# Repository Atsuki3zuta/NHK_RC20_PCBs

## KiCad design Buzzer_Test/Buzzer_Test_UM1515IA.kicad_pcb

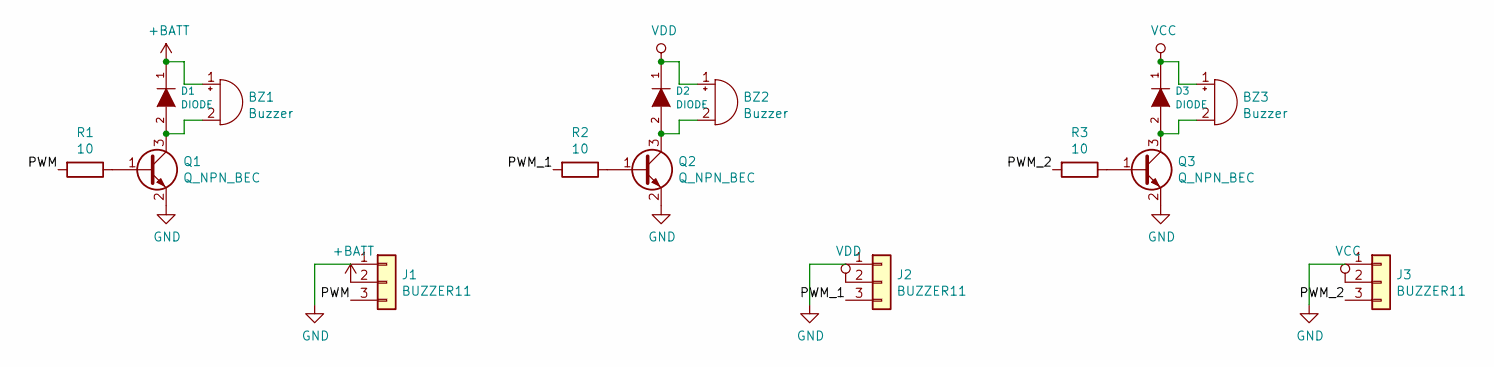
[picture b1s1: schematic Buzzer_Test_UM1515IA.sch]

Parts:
BZ1: Buzzer; UM1515IA
BZ2: Buzzer; UGCT7525AN4
BZ3: Buzzer; PKLCS1212E4001
D1, D2, D3: DIODE; D_SOD-123
J1, J2, J3: BUZZER11; PinHeader_1x03_P2.54mm_Vertical
Q1, Q2, Q3: Q_NPN_BEC; SOT-23W
R1, R2, R3: 10; R_0603_1608Metric

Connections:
+BATT: BZ1.1 (-), D1.1 (K), J1.2
/PWM: J1.3, R1.2
/PWM_1: J2.3, R2.2
/PWM_2: J3.3, R3.2
GND: J1.1, J2.1, J3.1, Q1.2 (E), Q2.2 (E), Q3.2 (E)
unnamed: BZ1.2 (+), D1.2 (A), Q1.3 (C)
unnamed: BZ2.2 (+), D2.2 (A), Q2.3 (C)
unnamed: BZ3.2 (+), D3.2 (A), Q3.3 (C)
unnamed: Q1.1 (B), R1.1
unnamed: Q2.1 (B), R2.1
unnamed: Q3.1 (B), R3.1
VCC: BZ3.1 (-), D3.1 (K), J3.2
VDD: BZ2.1 (-), D2.1 (K), J2.2

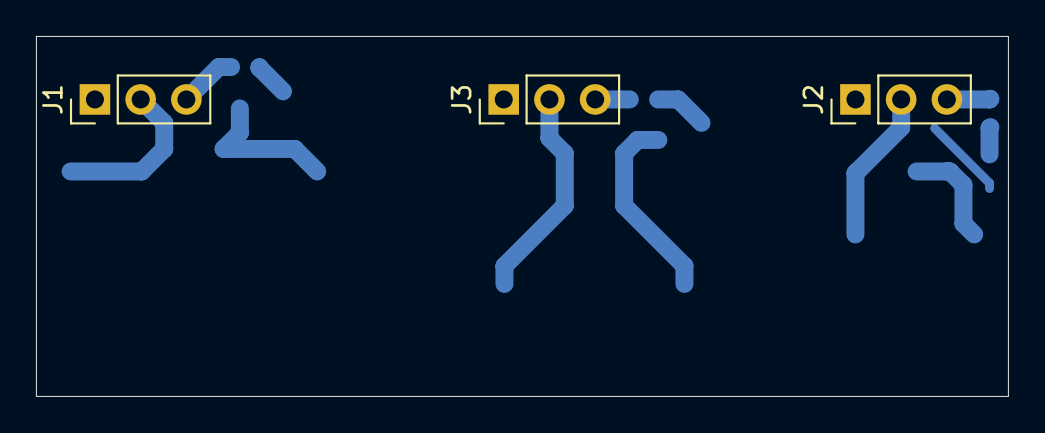
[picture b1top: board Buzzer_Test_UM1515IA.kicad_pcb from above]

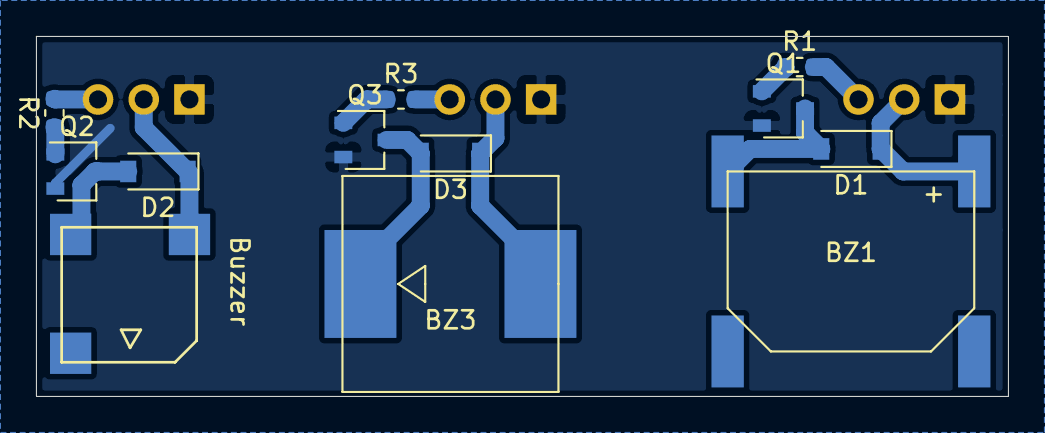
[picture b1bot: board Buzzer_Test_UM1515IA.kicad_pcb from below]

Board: 2 copper layers, 54.0 x 20.0 mm, 15 parts (12 on the bottom side), 13 nets.

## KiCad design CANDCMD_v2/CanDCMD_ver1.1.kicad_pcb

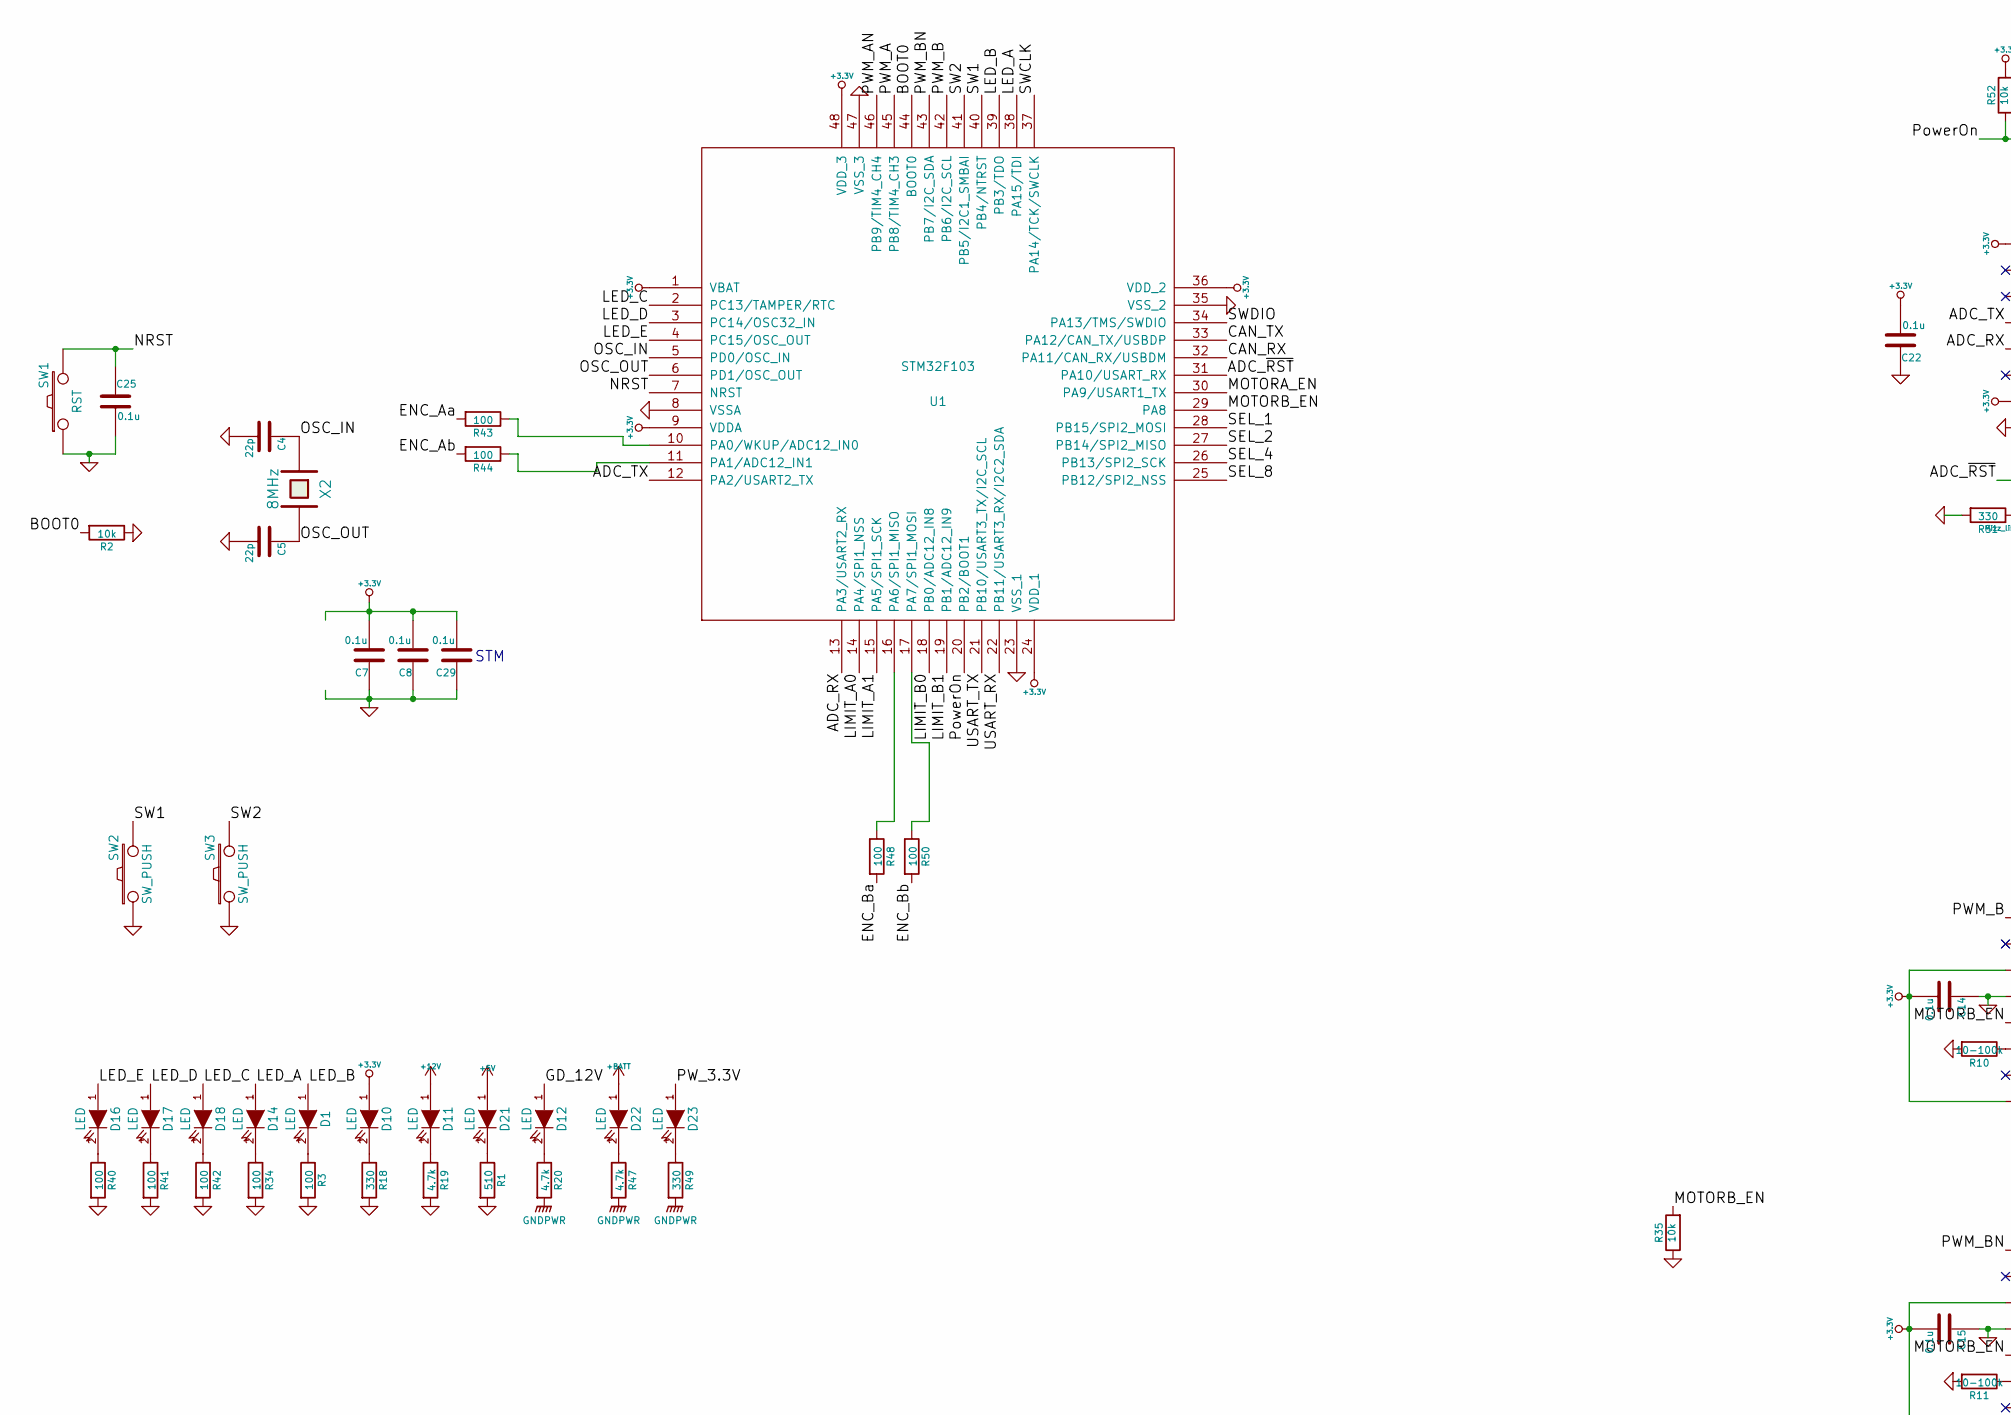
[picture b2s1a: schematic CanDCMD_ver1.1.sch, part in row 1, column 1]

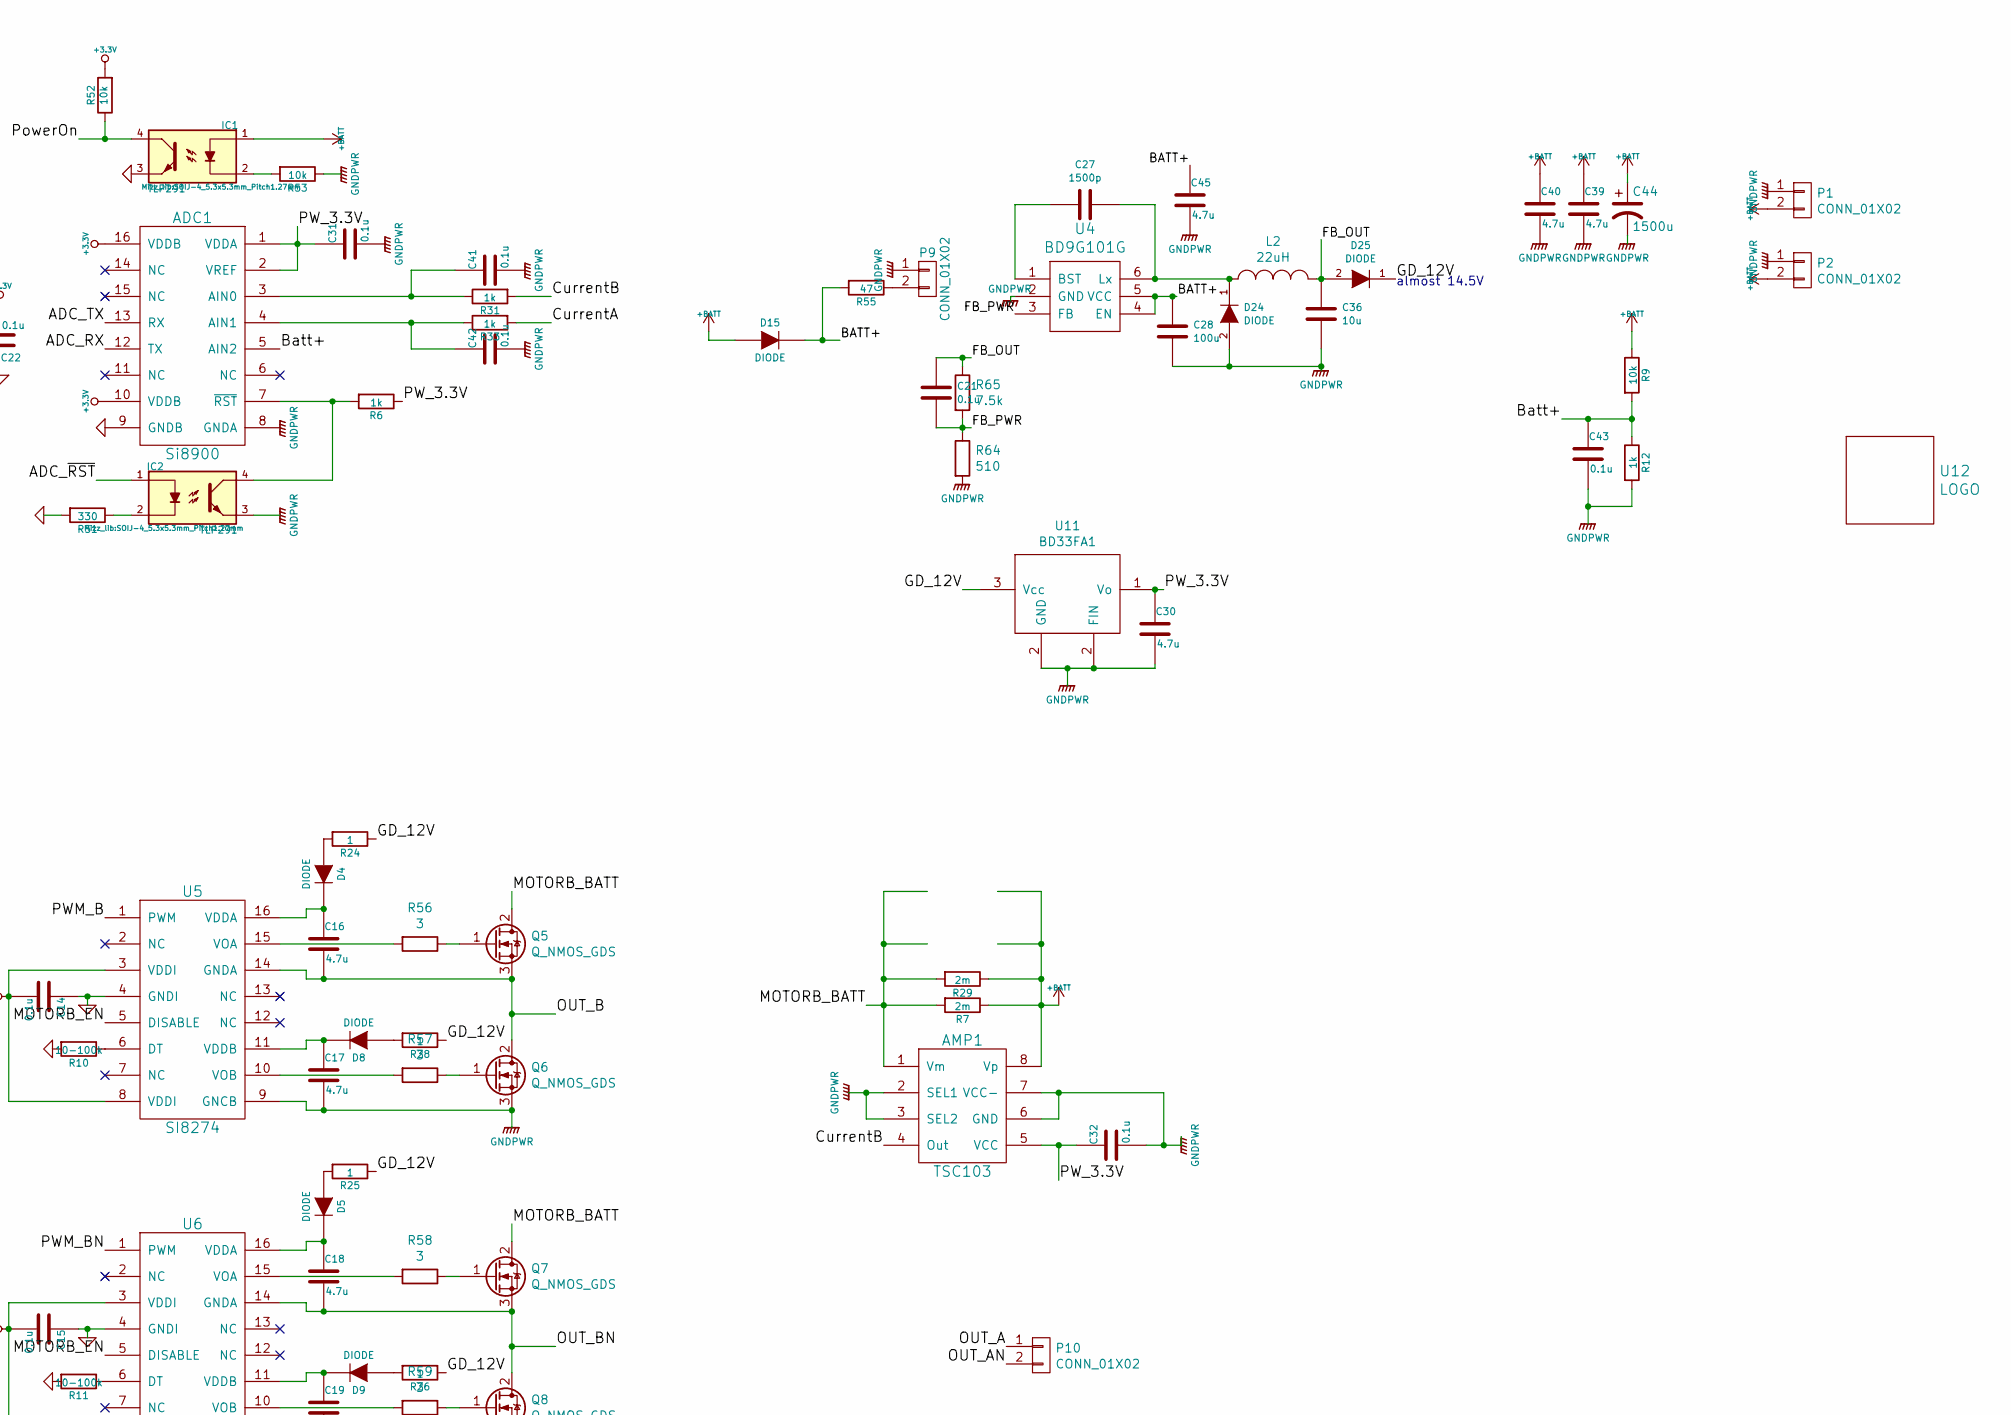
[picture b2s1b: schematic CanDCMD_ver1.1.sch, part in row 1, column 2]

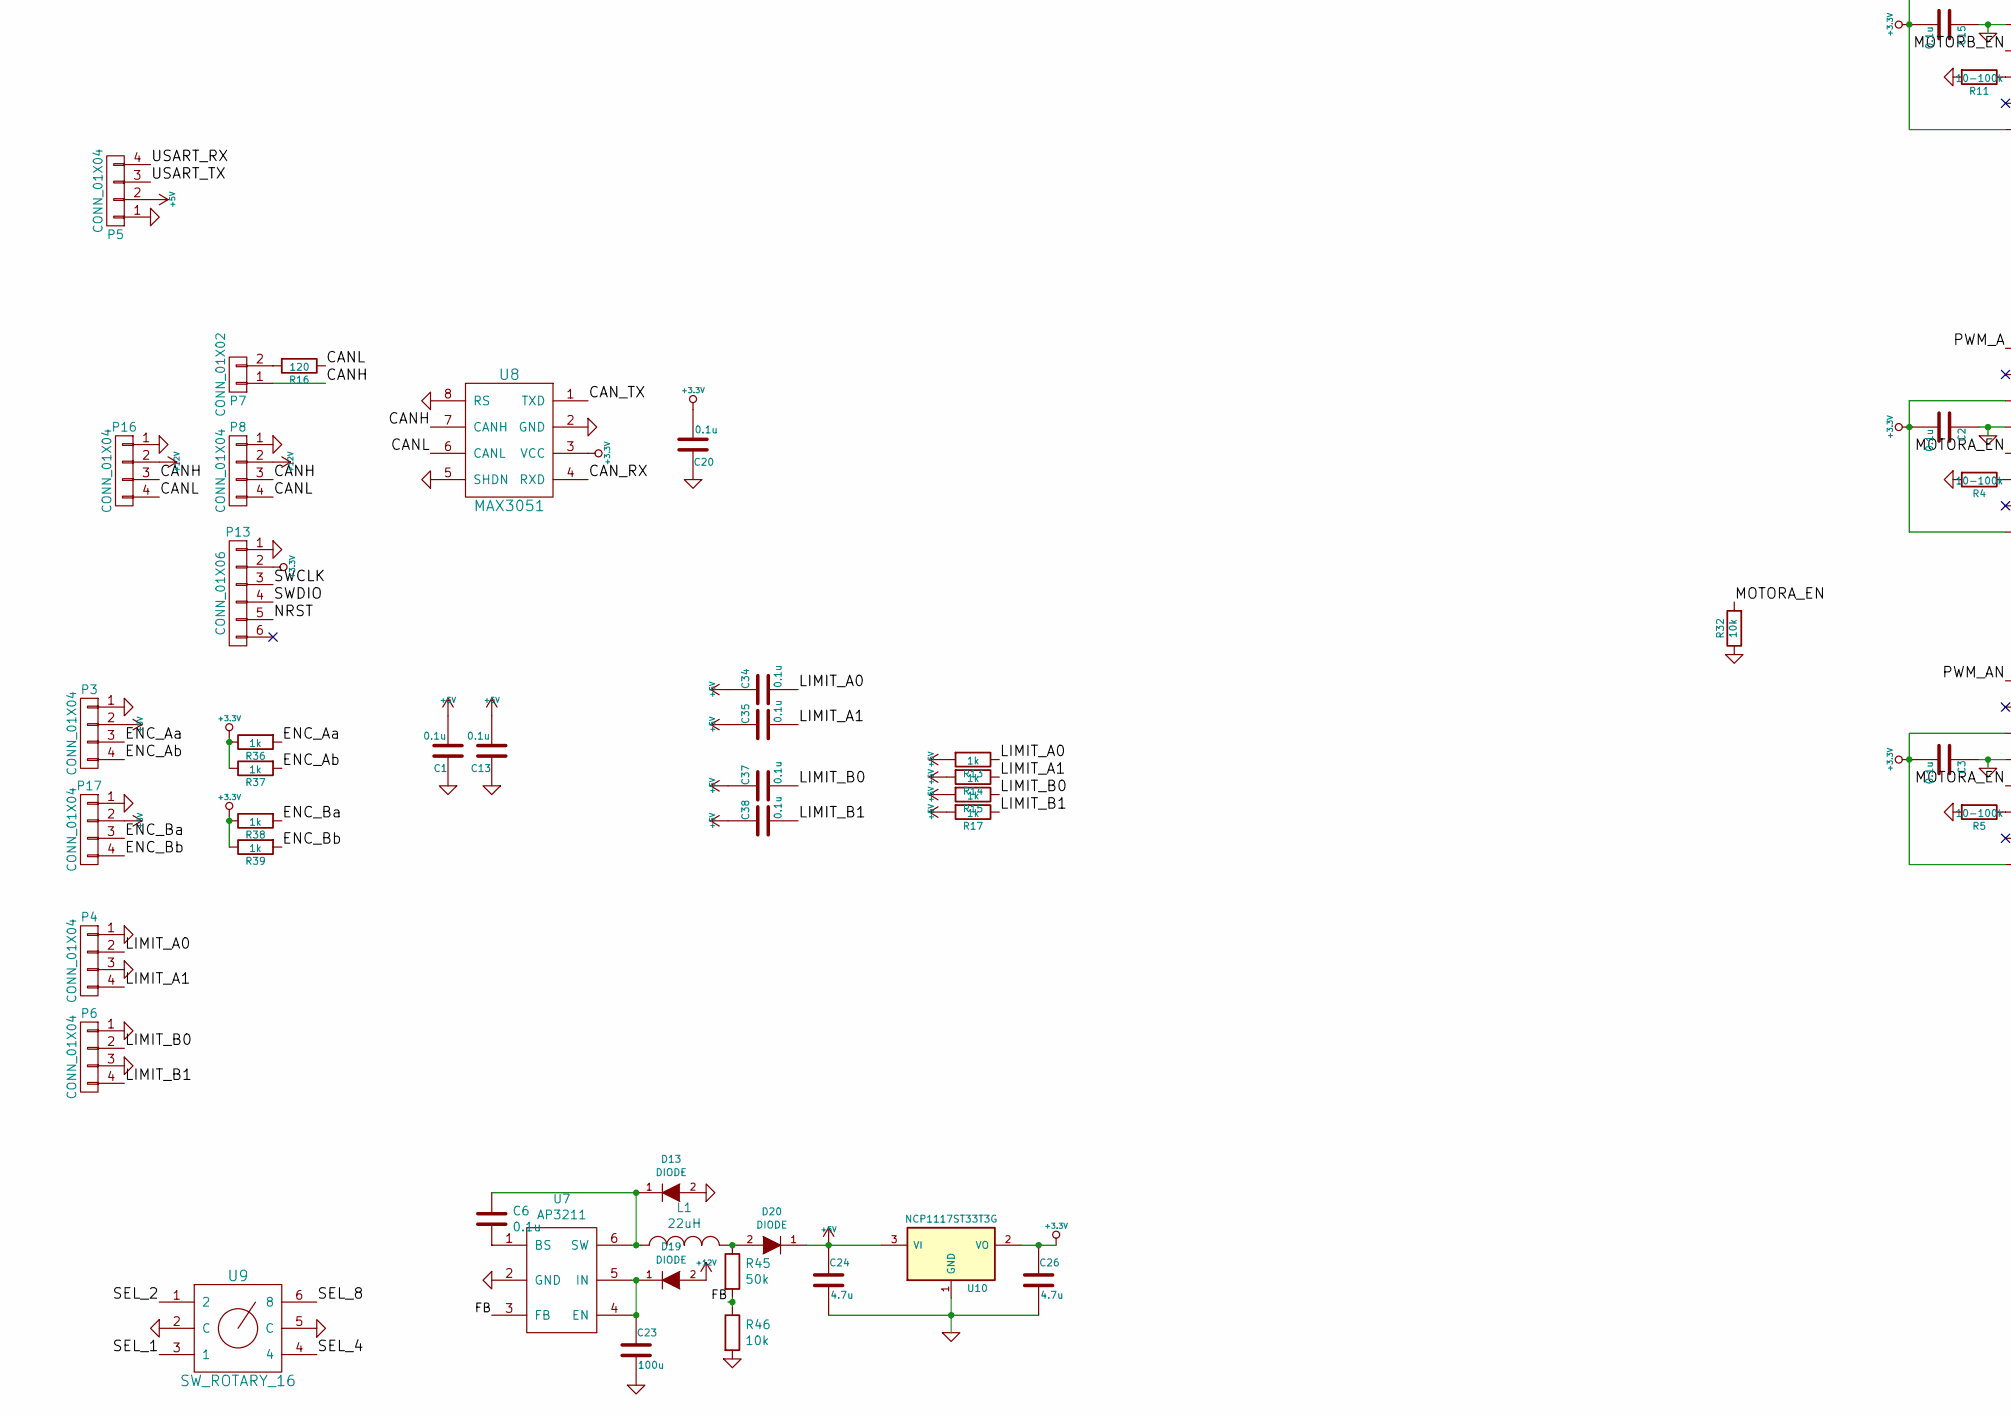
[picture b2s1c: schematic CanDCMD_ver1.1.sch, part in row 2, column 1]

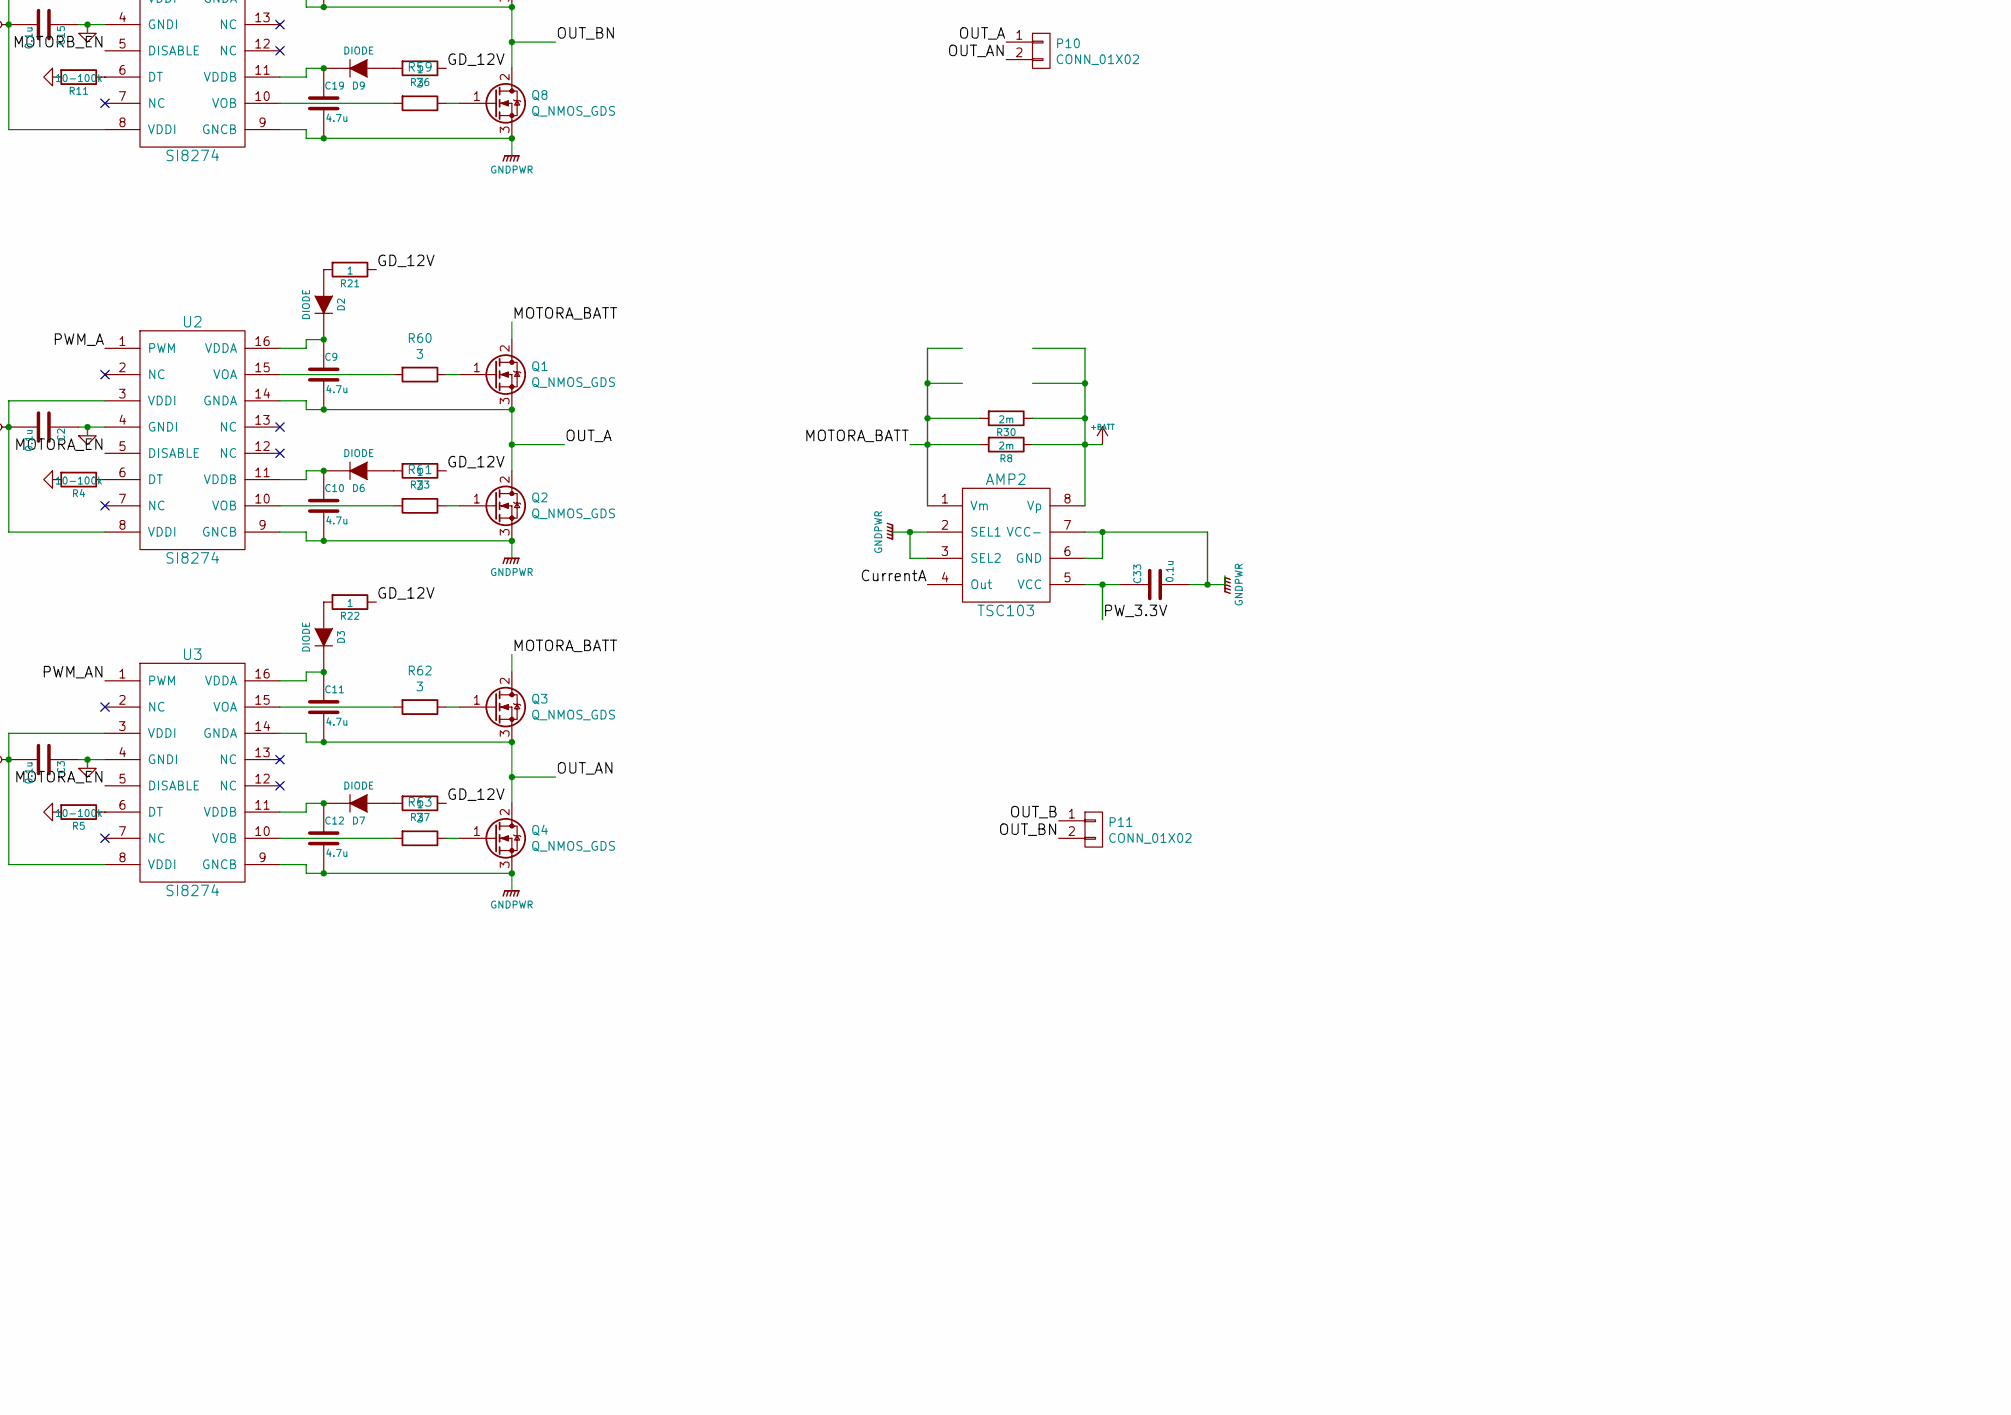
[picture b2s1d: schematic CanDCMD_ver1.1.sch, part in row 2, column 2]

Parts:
ADC1: Si8900; SOIC-16W_7.5x10.3mm_P1.27mm
AMP1, AMP2: TSC103; SOIC-8_3.9x4.9mm_P1.27mm
C1, C2, C3, C6, C7, C8, C13, C14, C15, C20, C21, C22, C25, C29, C31, C32, C33, C34, C35, C37, C38, C41, C42, C43: 0.1u; C_0603_1608Metric
C4, C5: 22p; C_0603_1608Metric
C9, C10, C11, C12, C16, C17, C18, C19: 4.7u; C_1206_3216Metric
C23, C28: 100u; C_Radial_D6.3mm_H11.0mm_P2.50mm
C24, C26, C30, C39, C40, C45: 4.7u; C_0805_2012Metric
C27: 1500p; C_0603_1608Metric
C36: 10u; C_0805_2012Metric
C44: 1500u; C_Radial_D12.5mm_H25.0mm_P5.00mm
D1, D10, D11, D12, D14, D16, D17, D18, D21, D22, D23: LED; LED_0603_1608Metric
D2, D3, D4, D5, D6, D7, D8, D9: DIODE; D_0603_1608Metric
D13, D19, D20, D24, D25: DIODE; D_SOD-123
D15: DIODE; D_1206_3216Metric
IC1, IC2: TLP291; SOIJ-4_5.3x5.3mm_Pitch1.27mm
L1, L2: 22uH; L_Taiyo-Yuden_NR-50xx_HandSoldering
P1: CONN_01X02; XT60_M
P2, P10, P11: CONN_01X02; XT60_F
P3, P4, P6, P8, P16, P17: CONN_01X04; XA_4LC
P5: CONN_01X04; PinSocket_1x04_P2.54mm_Vertical
P7: CONN_01X02; PinHeader_1x02_P2.54mm_Vertical
P9: CONN_01X02; XA_2P
P13: CONN_01X06; ZH_6P
Q1, Q2, Q3, Q4, Q5, Q6, Q7, Q8: Q_NMOS_GDS; TO-263-2
R1, R64: 510; R_0603_1608Metric
R2, R9, R32, R35, R46, R52, R53: 10k; R_0603_1608Metric
R3, R34, R40, R41, R42, R43, R44, R48, R50: 100; R_0603_1608Metric
R4, R5, R10, R11: 10-100k; R_0603_1608Metric
R6, R12, R13, R14, R15, R17, R31, R33, R36, R37, R38, R39: 1k; R_0603_1608Metric
R7, R8, R29, R30: 2m; R_2010_5025Metric
R16: 120; R_0603_1608Metric
R18, R49, R51: 330; R_0603_1608Metric
R19, R20, R47: 4.7k; R_0603_1608Metric
R21, R22, R23, R24, R25, R26, R27, R28: 1; R_0603_1608Metric
R45: 50k; R_0603_1608Metric
R55: 47; R_2812
R56, R57, R58, R59, R60, R61, R62, R63: 3; R_0603_1608Metric
R65: 7.5k; R_0603_1608Metric
SW1: RST; SMD_Button
SW2, SW3: SW_PUSH; SMD_Button
U1: STM32F103; LQFP-48_7x7mm_P0.5mm
U2, U3, U5, U6: SI8274; SOIC-16_3.9x9.9mm_P1.27mm
U4: BD9G101G; TSOP-6_1.65x3.05mm_P0.95mm
U7: AP3211; TSOP-6_1.65x3.05mm_P0.95mm
U8: MAX3051; SOIC-8_3.9x4.9mm_P1.27mm
U9: SW_ROTARY_16; rotary_0F
U10: NCP1117ST33T3G; SOT-223-3_TabPin2
U11: BD33FA1; SOT-89-3_Handsoldering
U12: LOGO; Mini_Monster
X2: 8MHz; Crystal_SMD_5032_2Pads

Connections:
+3.3V: ADC1.10 (VDDB), ADC1.16 (VDDB), C2.2, C3.2, C7.2, C8.2, C14.2, C15.2, C20.2, C22.2, C26.1, C29.2, D10.1 (A), P13.2, R36.1, R37.1, R38.1, R39.1, R52.2, U1.1 (VBAT), U1.9 (VDDA), U1.24 (VDD_1), U1.36 (VDD_2), U1.48 (VDD_3), U2.3 (VDDI), U2.8 (VDDI), U3.3 (VDDI), U3.8 (VDDI), U5.3 (VDDI), U5.8 (VDDI), U6.3 (VDDI), U6.8 (VDDI), U8.3 (VCC), U10.2 (VO)
+5V: C1.2, C13.2, C24.1, C34.1, C35.1, C37.1, C38.1, D20.1 (K), D21.1 (A), P3.2, P5.2, P17.2, R13.2, R14.2, R15.2, R17.2, U10.3 (VI)
+12V: D11.1 (A), D19.2 (A), P8.2, P16.2
+BATT: AMP1.8 (Vp), AMP2.8 (Vp), C39.1, C40.1, C44.1, D15.1 (A), D22.1 (A), IC1.1, P1.2, P2.2, R7.1, R8.1, R9.1, R29.1, R30.1
/ADC_RX: ADC1.12 (TX), U1.13 (PA3/USART2_RX)
/ADC_TX: ADC1.13 (RX), U1.12 (PA2/USART2_TX)
/ADC_~RST: IC2.1, U1.31 (PA10/USART_RX)
/BATT+: C28.1, C45.1, D15.2 (K), R55.2, U4.4 (EN), U4.5 (VCC)
/BOOT0: R2.2, U1.44 (BOOT0)
/Batt+: ADC1.5 (AIN2), C43.1, R9.2, R12.1
/CANH: P7.1, P8.3, P16.3, U8.7 (CANH)
/CANL: P8.4, P16.4, R16.1, U8.6 (CANL)
/CAN_RX: U1.32 (PA11/CAN_RX/USBDM), U8.4 (RXD)
/CAN_TX: U1.33 (PA12/CAN_TX/USBDP), U8.1 (TXD)
/CurrentA: AMP2.4 (Out), R33.2
/CurrentB: AMP1.4 (Out), R31.2
/ENC_Aa: P3.3, R36.2, R43.2
/ENC_Ab: P3.4, R37.2, R44.2
/ENC_Ba: P17.3, R38.2, R48.2
/ENC_Bb: P17.4, R39.2, R50.2
/FB: R45.2, R46.1, U7.3 (FB)
/FB_OUT: C21.1, C36.1, D25.2 (A), L2.2, R65.1
/FB_PWR: C21.2, R64.1, R65.2, U4.3 (FB)
/GD_12V: D12.1 (A), D25.1 (K), R21.1, R22.1, R23.1, R24.1, R25.1, R26.1, R27.1, R28.1, U11.3 (Vcc)
/LED_A: D14.1 (A), U1.38 (PA15/TDI)
/LED_B: D1.1 (A), U1.39 (PB3/TDO)
/LED_C: D18.1 (A), U1.2 (PC13/TAMPER/RTC)
/LED_D: D17.1 (A), U1.3 (PC14/OSC32_IN)
/LED_E: D16.1 (A), U1.4 (PC15/OSC_OUT)
/LIMIT_A0: C34.2, P4.2, R13.1, U1.14 (PA4/SPI1_NSS)
/LIMIT_A1: C35.2, P4.4, R14.1, U1.15 (PA5/SPI1_SCK)
/LIMIT_B0: C37.2, P6.2, R15.1, U1.18 (PB0/ADC12_IN8)
/LIMIT_B1: C38.2, P6.4, R17.1, U1.19 (PB1/ADC12_IN9)
/MOTORA_BATT: AMP2.1 (Vm), Q1.2 (D), Q3.2 (D), R8.2, R30.2
/MOTORA_EN: R32.2, U1.30 (PA9/USART1_TX), U2.5 (DISABLE), U3.5 (DISABLE)
/MOTORB_BATT: AMP1.1 (Vm), Q5.2 (D), Q7.2 (D), R7.2, R29.2
/MOTORB_EN: R35.2, U1.29 (PA8), U5.5 (DISABLE), U6.5 (DISABLE)
/NRST: C25.1, P13.5, SW1.2, U1.7 (NRST)
/OSC_IN: C4.1, U1.5 (PD0/OSC_IN), X2.1
/OSC_OUT: C5.1, U1.6 (PD1/OSC_OUT), X2.2
/OUT_A: C9.2, P10.1, Q1.3 (S), Q2.2 (D), U2.14 (GNDA)
/OUT_AN: C11.2, P10.2, Q3.3 (S), Q4.2 (D), U3.14 (GNDA)
/OUT_B: C16.2, P11.1, Q5.3 (S), Q6.2 (D), U5.14 (GNDA)
/OUT_BN: C18.2, P11.2, Q7.3 (S), Q8.2 (D), U6.14 (GNDA)
/PWM_A: U1.45 (PB8/TIM4_CH3), U2.1 (PWM)
/PWM_AN: U1.46 (PB9/TIM4_CH4), U3.1 (PWM)
/PWM_B: U1.42 (PB6/I2C_SCL), U5.1 (PWM)
/PWM_BN: U1.43 (PB7/I2C_SDA), U6.1 (PWM)
/PW_3.3V: ADC1.1 (VDDA), ADC1.2 (VREF), AMP1.5 (VCC), AMP2.5 (VCC), C30.1, C31.1, C32.1, C33.1, D23.1 (A), R6.1, U11.1 (Vo)
/PowerOn: IC1.4, R52.1, U1.20 (PB2/BOOT1)
/SEL_1: U1.28 (PB15/SPI2_MOSI), U9.3 (1)
/SEL_2: U1.27 (PB14/SPI2_MISO), U9.1 (2)
/SEL_4: U1.26 (PB13/SPI2_SCK), U9.4
/SEL_8: U1.25 (PB12/SPI2_NSS), U9.6 (8)
/SW1: SW2.2, U1.40 (PB4/NTRST)
/SW2: SW3.2, U1.41 (PB5/I2C1_SMBAI)
/SWCLK: P13.3, U1.37 (PA14/TCK/SWCLK)
/SWDIO: P13.4, U1.34 (PA13/TMS/SWDIO)
/USART_RX: P5.4, U1.22 (PB11/USART3_RX/I2C2_SDA)
/USART_TX: P5.3, U1.21 (PB10/USART3_TX/I2C_SCL)
GND: ADC1.9 (GNDB), C1.1, C2.1, C3.1, C4.2, C5.2, C7.1, C8.1, C13.1, C14.1, C15.1, C20.1, C22.1, C23.2, C24.2, C25.2, C26.2, C29.1, D13.2 (A), IC1.3, P3.1, P4.1, P4.3, P5.1, P6.1, P6.3, P8.1, P13.1, P16.1, P17.1, R1.2, R2.1, R3.2, R4.2, R5.2, R10.2, R11.2, R18.2, R19.2, R32.1, R34.2, R35.1, R40.2, R41.2, R42.2, R46.2, R51.2, SW1.1, SW2.1, SW3.1, U1.8 (VSSA), U1.23 (VSS_1), U1.35 (VSS_2), U1.47 (VSS_3), U2.4 (GNDI), U3.4 (GNDI), U5.4 (GNDI), U6.4 (GNDI), U7.2 (GND), U8.2 (GND), U8.5 (SHDN), U8.8 (RS), U9.2 (C), U9.5 (C), U10.1 (GND)
GNDPWR: ADC1.8 (GNDA), AMP1.2 (SEL1), AMP1.3 (SEL2), AMP1.6 (GND), AMP1.7 (VCC-), AMP2.2 (SEL1), AMP2.3 (SEL2), AMP2.6 (GND), AMP2.7 (VCC-), C10.2, C12.2, C17.2, C19.2, C28.2, C30.2, C31.2, C32.2, C33.2, C36.2, C39.2, C40.2, C41.2, C42.2, C43.2, C44.2, C45.2, D24.2 (A), IC2.3, P1.1, P2.1, P9.1, Q2.3 (S), Q4.3 (S), Q6.3 (S), Q8.3 (S), R12.2, R20.2, R47.2, R49.2, R53.1, R64.2, U2.9 (GNCB), U3.9 (GNCB), U4.2 (GND), U5.9 (GNCB), U6.9 (GNCB), U11.2 (FIN)
unnamed: ADC1.3 (AIN0), C41.1, R31.1
unnamed: ADC1.4 (AIN1), C42.1, R33.1
unnamed: ADC1.7 (~RST), IC2.4, R6.2
unnamed: C6.1, D13.1 (K), L1.1, U7.6 (SW)
unnamed: C6.2, U7.1 (BS)
unnamed: C9.1, D2.2 (K), U2.16 (VDDA)
unnamed: C10.1, D6.2 (K), U2.11 (VDDB)
unnamed: C11.1, D3.2 (K), U3.16 (VDDA)
unnamed: C12.1, D7.2 (K), U3.11 (VDDB)
unnamed: C16.1, D4.2 (K), U5.16 (VDDA)
unnamed: C17.1, D8.2 (K), U5.11 (VDDB)
unnamed: C18.1, D5.2 (K), U6.16 (VDDA)
unnamed: C19.1, D9.2 (K), U6.11 (VDDB)
unnamed: C23.1, D19.1 (K), U7.4 (EN), U7.5 (IN)
unnamed: C27.1, D24.1 (K), L2.1, U4.6 (Lx)
unnamed: C27.2, U4.1 (BST)
unnamed: D1.2 (K), R3.1
unnamed: D2.1 (A), R21.2
unnamed: D3.1 (A), R22.2
unnamed: D4.1 (A), R24.2
unnamed: D5.1 (A), R25.2
unnamed: D6.1 (A), R23.2
unnamed: D7.1 (A), R27.2
unnamed: D8.1 (A), R28.2
unnamed: D9.1 (A), R26.2
unnamed: D10.2 (K), R18.1
unnamed: D11.2 (K), R19.1
unnamed: D12.2 (K), R20.1
unnamed: D14.2 (K), R34.1
unnamed: D16.2 (K), R40.1
unnamed: D17.2 (K), R41.1
unnamed: D18.2 (K), R42.1
unnamed: D20.2 (A), L1.2, R45.1
unnamed: D21.2 (K), R1.1
unnamed: D22.2 (K), R47.1
unnamed: D23.2 (K), R49.1
unnamed: IC1.2, R53.2
unnamed: IC2.2, R51.1
unnamed: P7.2, R16.2
unnamed: P9.2, R55.1
unnamed: Q1.1 (G), R60.1
unnamed: Q2.1 (G), R61.1
unnamed: Q3.1 (G), R62.1
unnamed: Q4.1 (G), R63.1
unnamed: Q5.1 (G), R56.1
unnamed: Q6.1 (G), R57.1
unnamed: Q7.1 (G), R58.1
unnamed: Q8.1 (G), R59.1
unnamed: R4.1, U2.6 (DT)
unnamed: R5.1, U3.6 (DT)
unnamed: R10.1, U5.6 (DT)
unnamed: R11.1, U6.6 (DT)
unnamed: R43.1, U1.10 (PA0/WKUP/ADC12_IN0)
unnamed: R44.1, U1.11 (PA1/ADC12_IN1)
unnamed: R48.1, U1.16 (PA6/SPI1_MISO)
unnamed: R50.1, U1.17 (PA7/SPI1_MOSI)
unnamed: R56.2, U5.15 (VOA)
unnamed: R57.2, U5.10 (VOB)
unnamed: R58.2, U6.15 (VOA)
unnamed: R59.2, U6.10 (VOB)
unnamed: R60.2, U2.15 (VOA)
unnamed: R61.2, U2.10 (VOB)
unnamed: R62.2, U3.15 (VOA)
unnamed: R63.2, U3.10 (VOB)

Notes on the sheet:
STM
almost 14.5V

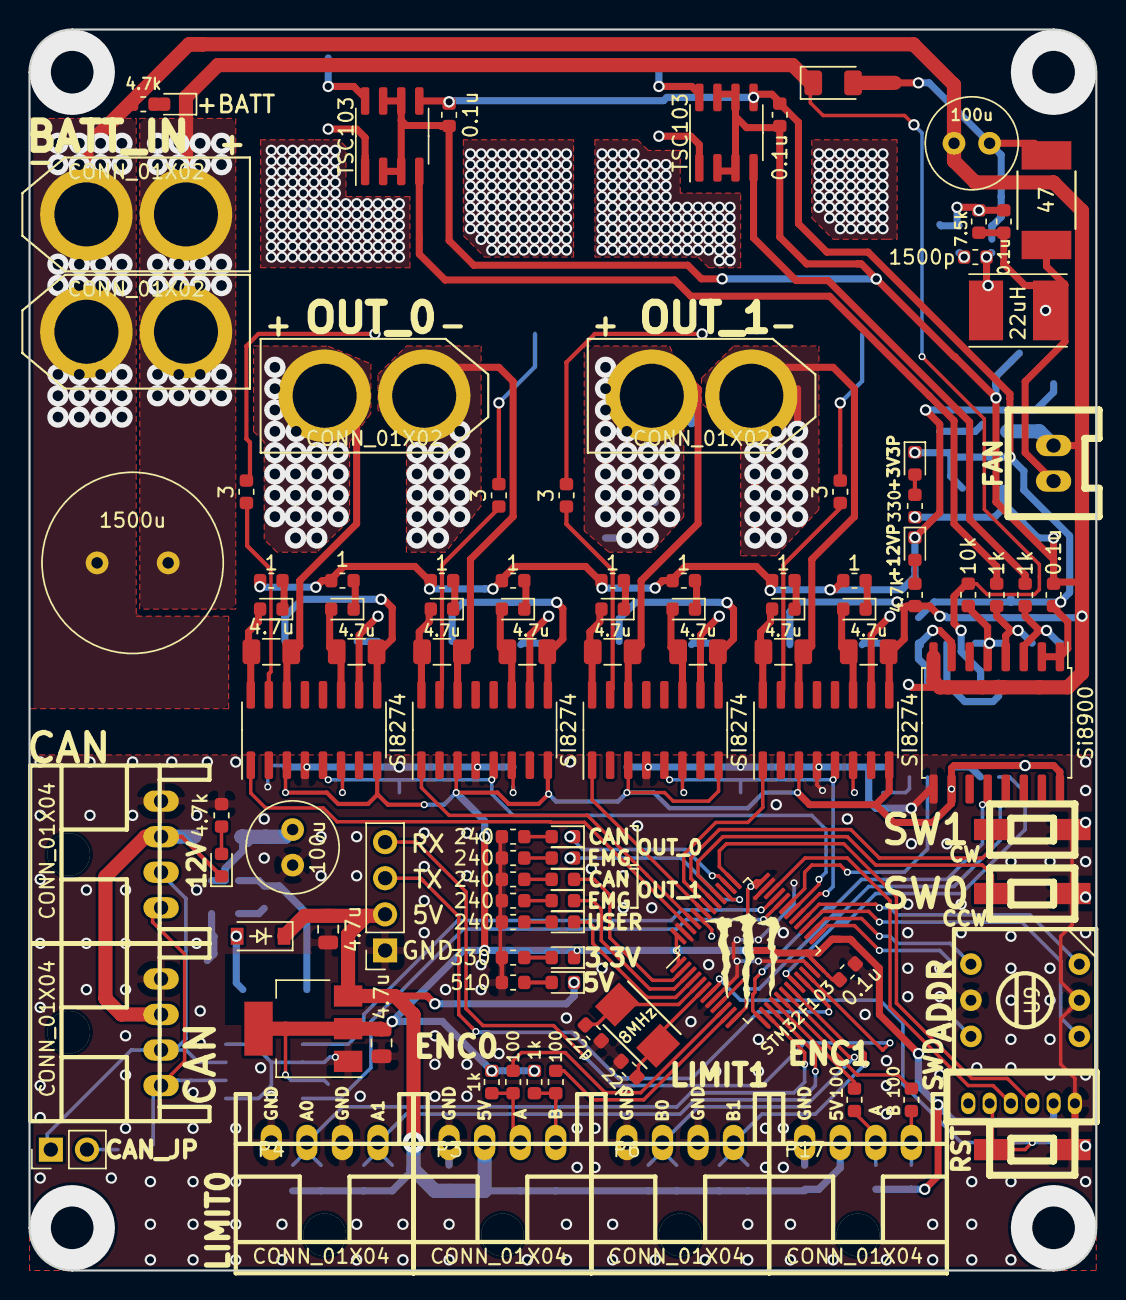
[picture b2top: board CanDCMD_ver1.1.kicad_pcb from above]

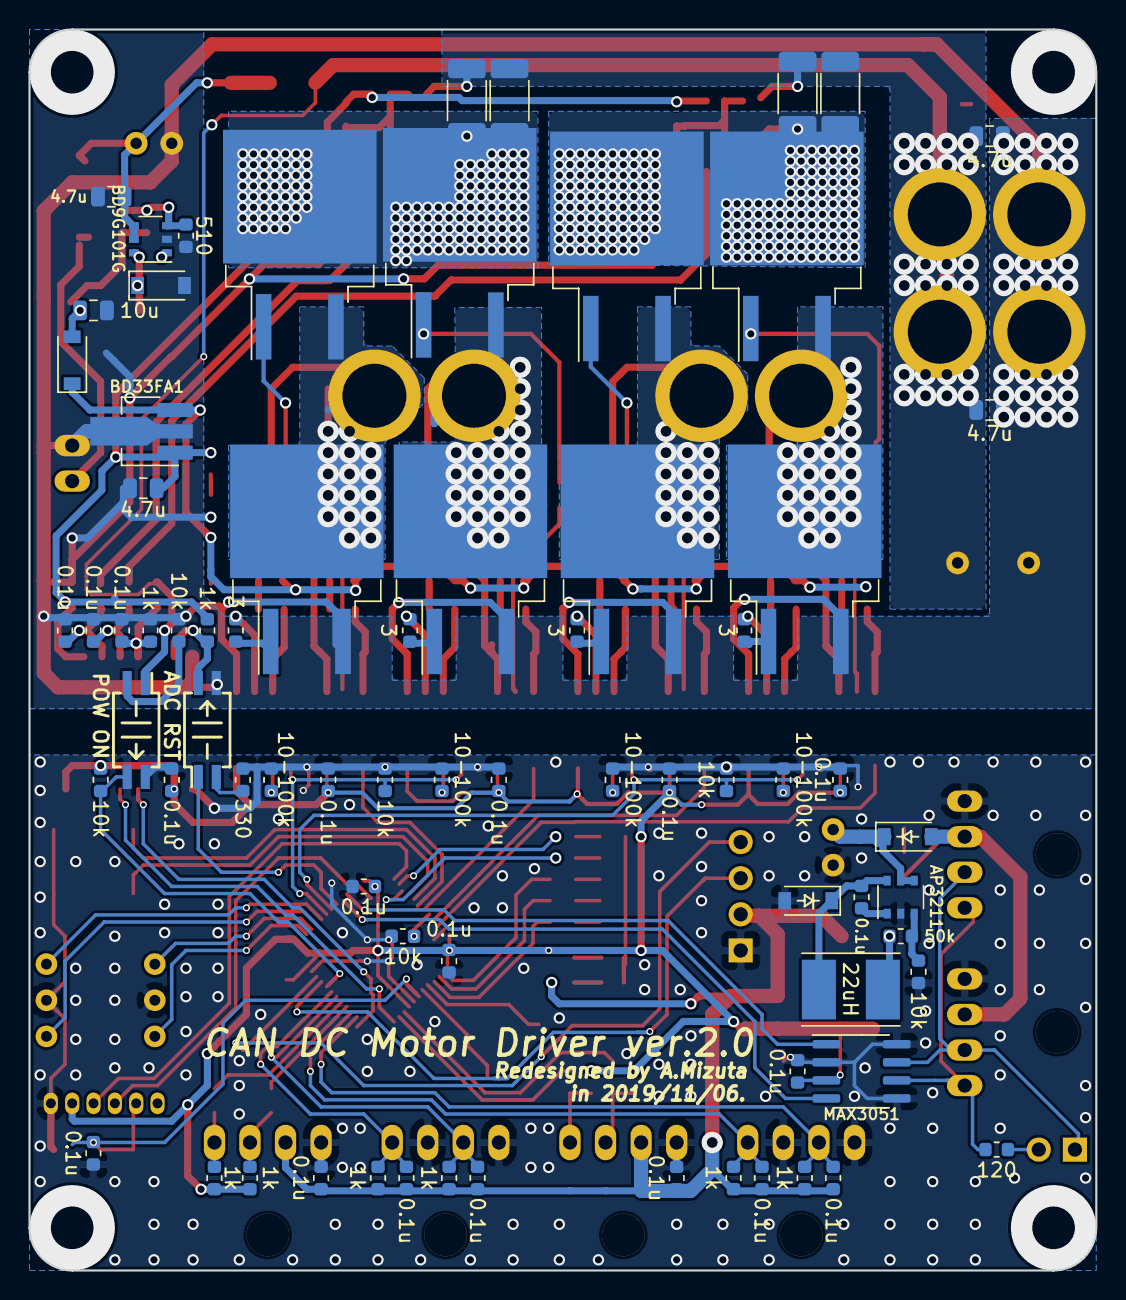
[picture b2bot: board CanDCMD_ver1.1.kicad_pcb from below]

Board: 2 copper layers, 75.0 x 87.2 mm, 179 parts (73 on the bottom side), 126 nets.
